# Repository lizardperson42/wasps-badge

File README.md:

# wasps-badge

The [WASPS](https://wasp.systems) electronic badge.

## Hardware

CAD files for the hardware are provided in KiCad format in `wasps-badge/`.

### Connectors / Pinout

The badge features three 0.1in-pitch pin headers. Their silkscreen markings
are partially absent or obscured; Pin 1 can be recognized by its square pad.
Their locations are given as in the design files, where the mounting hole is
on top, looking at the front of the board.

| Header | Location    | Description          |
| ------ | ----------- | -------------------- |
| J1     | Bottom      | Flashing connector   |
| J2     | Bottom left | CTF breakout         |
| J3     | Top right   | Shitty Add-On Header |

Pinouts:

| Header | Pin    | MCU pin    | Description                          |
| ------ | ------ | ---------- | ------------------------------------ |
| J1     | 1      | GND        | GND                                  |
| J1     | 2      | VDD        | 3.3V                                 |
| J1     | 3      | SWIO / PD1 | SWIO (MCU flashing connection)       |
| J1     | 4      | NRST / PD7 | RST (active-low MCU reset)           |
| J2     | 1      | GND        | GND                                  |
| J2     | 2      | PD0        | "Press me" button (pulled up by MCU) |
| J2     | 3      | PD3        | "Now" LED                            |
| J2     | 4      | PD5        | "0" LED                              |
| J2     | 5      | PD6        | "1" LED                              |
| J3     | 1 (TL) | VDD        | 3.3V                                 |
| J3     | 2 (BL) | GND        | GND                                  |
| J3     | 3 (TC) | PC2        | I²C SCL line                         |
| J3     | 4 (BC) | PC1        | I²C SDA line                         |
| J3     | 5 (TR) | PC3        | GPIO                                 |
| J3     | 6 (BR) | PC4        | GPIO                                 |

On-board-only pinout:

| MCU pin    | Description                                                   |
| ---------- | ------------------------------------------------------------- |
| NRST / PD7 | "Reset" button                                                |
| PD4        | "Too slow" LED                                                |
| PC6        | Front RGB LEDs (WS2812B, chain length 2)                      |
| PC7        | Reverse-mounted back RGB LEDs (WS2812B, chain length 3, NRND) |

## Software

A PlatformIO project for a firmware adding basic blinkenlights can be found in
`code/`. Since field testing has indicated that the through-board LEDs are a
little too focused for the intended effect, they are not driven.

The code runs the MCU in a busy loop, limiting battery life. Pull requests to
improve energy efficiency are welcome.

CTF functionality is not included, pull requests welcome.

If you have issues with compiling the firmware, a pre-compiled image is
provided at `code/firmware.bin`. It can be flashed using the tool `rvprog`
like this:

    rvprog -f code/firmware.bin

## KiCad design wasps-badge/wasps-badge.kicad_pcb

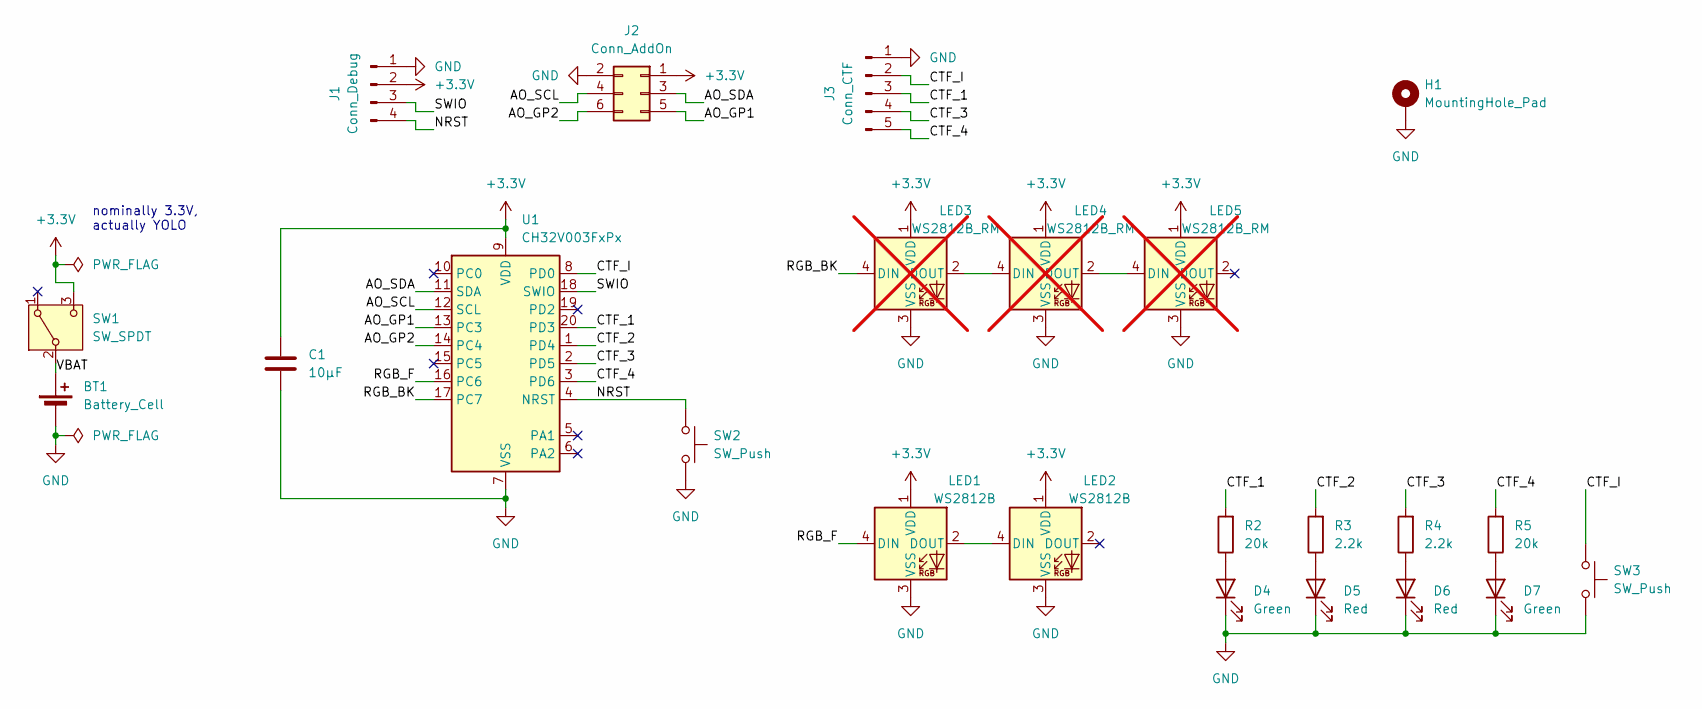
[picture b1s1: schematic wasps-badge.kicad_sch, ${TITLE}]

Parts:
BT1: Battery_Cell; BatteryHolder_Keystone_1060_1x2032; LCSC C70377
C1: 10µF; C_0603_1608Metric_Pad1.08x0.95mm_HandSolder; LCSC C19702
D4, D7: Green; LED_0603_1608Metric_Pad1.05x0.95mm_HandSolder; LCSC C12624
D5, D6: Red; LED_0603_1608Metric_Pad1.05x0.95mm_HandSolder; LCSC C965799
H1: MountingHole_Pad; MountingHole_3.2mm_M3_Pad
J1: Conn_Debug; PinHeader_1x04_P2.54mm_Vertical
J2: Conn_AddOn; PinSocket_2x03_P2.54mm_Vertical; LCSC C5116527
J3: Conn_CTF; PinHeader_1x05_P2.54mm_Vertical
LED1, LED2: WS2812B; LED_WS2812B_PLCC4_5.0x5.0mm_P3.2mm
LED3, LED4, LED5: WS2812B_RM; LED_WS2812B_Reverse; not fitted
R2, R5: 20k; R_0603_1608Metric_Pad0.98x0.95mm_HandSolder; LCSC C4184
R3, R4: 2.2k; R_0603_1608Metric_Pad0.98x0.95mm_HandSolder; LCSC C4190
SW1: SW_SPDT; SW_SPDT_MSS22D18_SMD; LCSC C41375971
SW2, SW3: SW_Push; SW_PUSH_L4.0-W3.0-LS5.0_SMD; LCSC C5221275
U1: CH32V003FxPx; TSSOP-20_4.4x6.5mm_P0.65mm; LCSC C5187096

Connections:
+3.3V: C1.1, J1.2, J2.1, LED1.1 (VDD), LED2.1 (VDD), LED3.1 (VDD), LED4.1 (VDD), LED5.1 (VDD), SW1.3 (C), U1.9 (VDD)
/AO_GP1: J2.5, U1.13 (PC3)
/AO_GP2: J2.6, U1.14 (PC4)
/AO_SCL: J2.4, U1.12 (SCL)
/AO_SDA: J2.3, U1.11 (SDA)
/CTF_1: J3.3, R2.2, U1.20 (PD3)
/CTF_2: R3.2, U1.1 (PD4)
/CTF_3: J3.4, R4.2, U1.2 (PD5)
/CTF_4: J3.5, R5.2, U1.3 (PD6)
/CTF_I: J3.2, SW3.1, U1.8 (PD0)
/NRST: J1.4, SW2.1, U1.4 (NRST)
/RGB_BK: LED3.4 (DIN), U1.17 (PC7)
/RGB_F: LED1.4 (DIN), U1.16 (PC6)
/SWIO: J1.3, U1.18 (SWIO)
/VBAT: BT1.1 (+), SW1.2 (B)
GND: BT1.2 (-), C1.2, D4.1 (K), D5.1 (K), D6.1 (K), D7.1 (K), H1.1, J1.1, J2.2, J3.1, LED1.3 (VSS), LED2.3 (VSS), LED3.3 (VSS), LED4.3 (VSS), LED5.3 (VSS), SW2.2, SW3.2, U1.7 (VSS)
unnamed: D4.2 (A), R2.1
unnamed: D5.2 (A), R3.1
unnamed: D6.2 (A), R4.1
unnamed: D7.2 (A), R5.1
unnamed: LED1.2 (DOUT), LED2.4 (DIN)
unnamed: LED3.2 (DOUT), LED4.4 (DIN)
unnamed: LED4.2 (DOUT), LED5.4 (DIN)

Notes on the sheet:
nominally 3.3V, actually YOLO

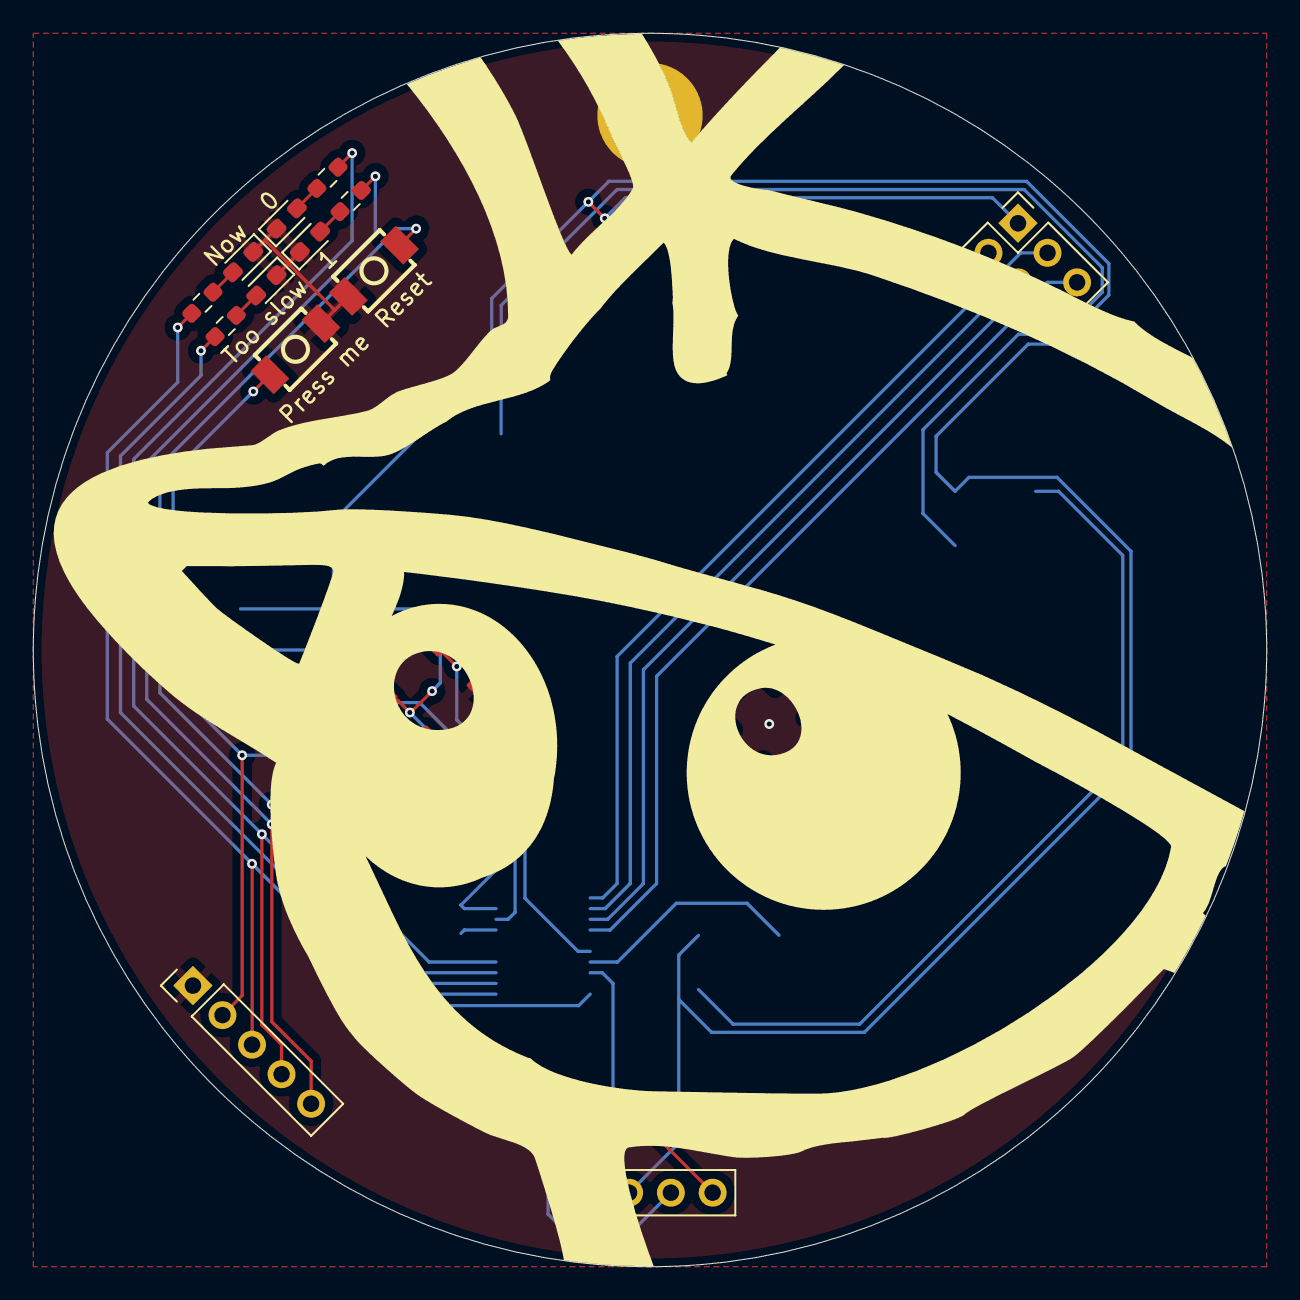
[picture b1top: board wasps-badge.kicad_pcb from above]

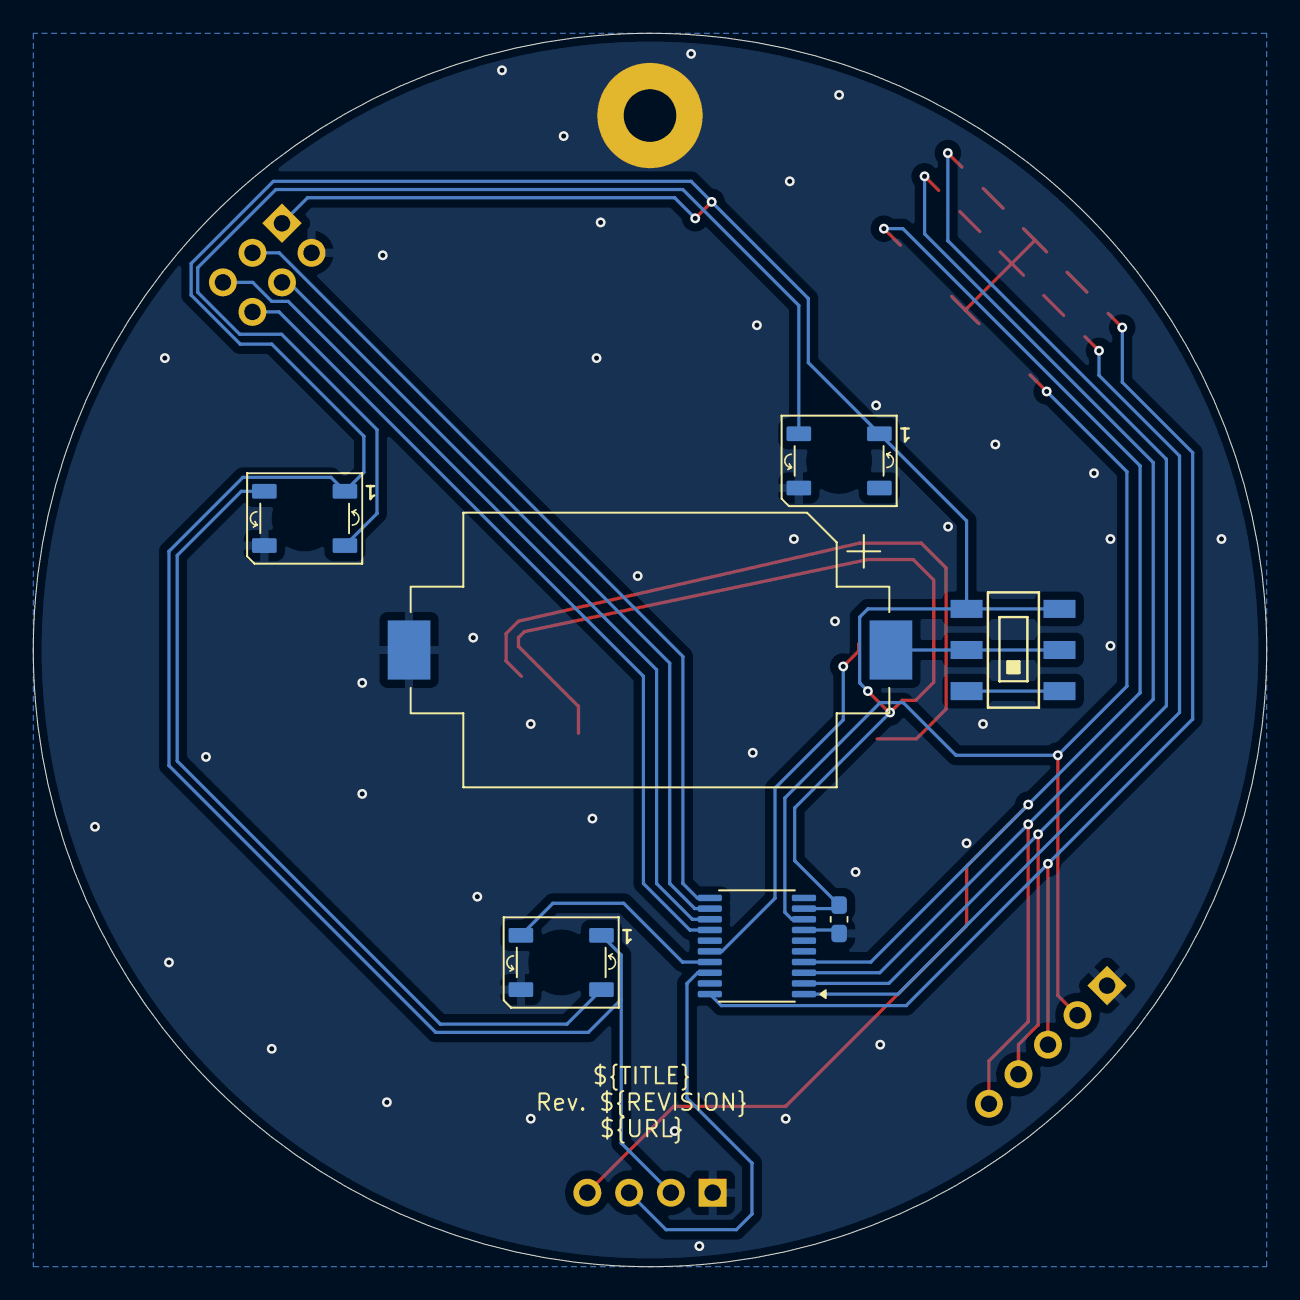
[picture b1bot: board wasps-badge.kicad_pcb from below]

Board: 2 copper layers, 75.0 x 75.0 mm, 24 parts (7 on the bottom side), 23 nets.

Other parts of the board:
BOARD: WaspFace

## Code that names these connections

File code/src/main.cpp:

#include <Arduino.h>

#include "ws2812.h"

struct FineHSV {
    uint16_t hue;
    uint8_t saturation;
    uint8_t value;

    static constexpr uint16_t MAX_HUE = 256 * 6;

    FineHSV(uint16_t hue, uint8_t saturation, uint8_t value) :
        hue(hue), saturation(saturation), value(value) {}

    operator Color() const {
        // <https://en.wikipedia.org/wiki/HSL_and_HSV#HSV_to_RGB>
        int chroma = value * saturation / 255;
        int complement = hue % (2 * 256);
        if (complement >= 256) complement = 512 - complement;
        complement = complement * chroma / 256;

        int r, g, b;
        if (hue < 256) {
            r = chroma    ; g = complement; b = 0         ;
        } else if (hue < 256 * 2) {
            r = complement; g = chroma    ; b = 0         ;
        } else if (hue < 256 * 3) {
            r = 0         ; g = chroma    ; b = complement;
        } else if (hue < 256 * 4) {
            r = 0         ; g = complement; b = chroma    ;
        } else if (hue < 256 * 5) {
            r = complement; g = 0         ; b = chroma    ;
        } else {
            r = chroma    ; g = 0         ; b = complement;
        }

        int whiten = value - chroma;
        return Color{ uint8_t(r + whiten),
                      uint8_t(g + whiten),
                      uint8_t(b + whiten) };
    }
};

class RainbowGenerator {
    Color &_output;
    uint16_t _counter;
    uint16_t _step;
    uint8_t _saturation;
    uint8_t _value;

public:
    RainbowGenerator(Color &output, uint16_t step,
                     uint8_t saturation, uint8_t value) :
        _output(output), _counter(0), _step(step),
        _saturation(saturation), _value(value) {}

    void step() {
        _output = FineHSV(_counter, _saturation, _value);
        _counter += _step;
        _counter %= FineHSV::MAX_HUE;
    }
};

#define PIN_LED_NOW   PD3
#define PIN_LED_2SLOW PD4
#define PIN_LED_0     PD5
#define PIN_LED_1     PD6

#define PIN_RGB_FRONT PC6
#define PIN_RGB_BACK  PC7

#define PIN_BUTTON    PD0

const int PINS[] = { PIN_LED_NOW, PIN_LED_0, PIN_LED_1, PIN_LED_2SLOW };

volatile unsigned counter = 0;

Color colors_front[2] = {};
WS2812 output_front(colors_front, { GPIOC, 6 });

RainbowGenerator rainbow[] = {
    { colors_front[0], FineHSV::MAX_HUE / 8 / 10, 255, 8 },
    { colors_front[1], FineHSV::MAX_HUE / 8 / 7, 255, 8 }
};

void resetCounter() {
    counter = 0;
}

void setup() {
    for (int pin : PINS) pinMode(pin, OUTPUT);
    pinMode(PIN_RGB_FRONT, OUTPUT);
    pinMode(PIN_BUTTON, INPUT_PULLUP);
    // The CH32V003 framework does not use the normal Arduino API. :(
    attachInterrupt(digitalPinToInterrupt(PIN_BUTTON), GPIO_Mode_IPU,
                    resetCounter, EXTI_Mode_Interrupt, EXTI_Trigger_Falling);
}

void loop() {
    unsigned curCounter = counter;
    if (curCounter < 8 * 5) {
        digitalWrite(PINS[curCounter & 3], !(curCounter >> 2 & 1));
        counter = curCounter + 1;
    }
    for (auto &r : rainbow) r.step();
    output_front.output();
    delay(125);
}

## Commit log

2025-12-13 Add .gitignore
2025-12-13 Import project state
2025-12-13 Add missing footprint assignments
2025-12-13 Change mounting hole pad name
    The footprint calls it "1", so "1" it is.
2025-12-13 Add cursed reverse-mounted RGB LED footprint
2025-12-15 First routing attempt; drop MISC header
2025-12-15 Fix CTF header position
2025-12-15 Add labeling
2025-12-15 Add more vias
2025-12-15 Update reverse-mount LED footprints
    Does this actually *do* anything?..
2025-12-15 Define resistor values
2025-12-16 Tweak LED5 location
    Maybe placing a raised ground pin close to... any of the battery's
    contacts is not *that* good an idea.
2025-12-16 Add supplier part numbers
2025-12-16 Adjust BOM settings
2025-12-28 Basic blinking
2025-12-28 More blinking
2025-12-28 Add RGB LED driving
2025-12-28 Drop back LEDs
    They *do* work, but not all that well.
2025-12-28 Add missing bit of WS2812 protocol
2025-12-28 Add non-RGB LED animation time limit
2025-12-29 Animate eyes more independently
2025-12-30 Add golden image
2025-12-30 Add more documentation
2025-12-30 Add pinout documentation
2025-12-30 Add disclaimer
2025-12-30 add CI action
2025-12-30 Bump actions/checkout from 5 to 6
    Bumps [actions/checkout](https://github.com/actions/checkout) from 5 to 6.
    - [Release notes](https://github.com/actions/checkout/releases)
    - [Changelog](https://github.com/actions/checkout/blob/main/CHANGELOG.md)
    - [Commits](https://github.com/actions/checkout/compare/v5...v6)
    ---
    updated-dependencies:
2025-12-30 Bump actions/upload-artifact from 4 to 6
    Bumps [actions/upload-artifact](https://github.com/actions/upload-artifact) from 4 to 6.
    - [Release notes](https://github.com/actions/upload-artifact/releases)
    - [Commits](https://github.com/actions/upload-artifact/compare/v4...v6)
    ---
    updated-dependencies:
    - dependency-name: actions/upload-artifact
2025-12-30 Add Makefile for code/
2025-12-30 Remove reverse-mount LEDs from BOM and placement
2025-12-30 Fix and improve Makefile
2025-12-30 Fix firmware.bin file permissions
    Unless CH32 microcontrollers get a *lot* more powerful, it is unlikely
    that the file will be natively executable whereever it is checked out.
2026-01-06 Complete pinout documentation
2026-02-20 Makefile: build through Docker
2026-02-20 switch to python:3.14, change target name and remove bash -c
2026-02-20 use docker -v .
2026-03-03 Bump actions/download-artifact from 7 to 8
    Bumps [actions/download-artifact](https://github.com/actions/download-artifact) from 7 to 8.
    - [Release notes](https://github.com/actions/download-artifact/releases)
    - [Commits](https://github.com/actions/download-artifact/compare/v7...v8)
    ---
    updated-dependencies:
    - dependency-name: actions/download-artifact
2026-03-03 Bump actions/upload-artifact from 6 to 7
    Bumps [actions/upload-artifact](https://github.com/actions/upload-artifact) from 6 to 7.
    - [Release notes](https://github.com/actions/upload-artifact/releases)
    - [Commits](https://github.com/actions/upload-artifact/compare/v6...v7)
    ---
    updated-dependencies:
    - dependency-name: actions/upload-artifact
2026-03-31 Bump actions/deploy-pages from 4 to 5
    Bumps [actions/deploy-pages](https://github.com/actions/deploy-pages) from 4 to 5.
    - [Release notes](https://github.com/actions/deploy-pages/releases)
    - [Commits](https://github.com/actions/deploy-pages/compare/v4...v5)
    ---
    updated-dependencies:
    - dependency-name: actions/deploy-pages
2026-04-14 Bump softprops/action-gh-release from 2 to 3
    Bumps [softprops/action-gh-release](https://github.com/softprops/action-gh-release) from 2 to 3.
    - [Release notes](https://github.com/softprops/action-gh-release/releases)
    - [Changelog](https://github.com/softprops/action-gh-release/blob/master/CHANGELOG.md)
    - [Commits](https://github.com/softprops/action-gh-release/compare/v2...v3)
    ---
    updated-dependencies:
2026-04-14 Bump actions/upload-pages-artifact from 4 to 5
    Bumps [actions/upload-pages-artifact](https://github.com/actions/upload-pages-artifact) from 4 to 5.
    - [Release notes](https://github.com/actions/upload-pages-artifact/releases)
    - [Commits](https://github.com/actions/upload-pages-artifact/compare/v4...v5)
    ---
    updated-dependencies:
    - dependency-name: actions/upload-pages-artifact
